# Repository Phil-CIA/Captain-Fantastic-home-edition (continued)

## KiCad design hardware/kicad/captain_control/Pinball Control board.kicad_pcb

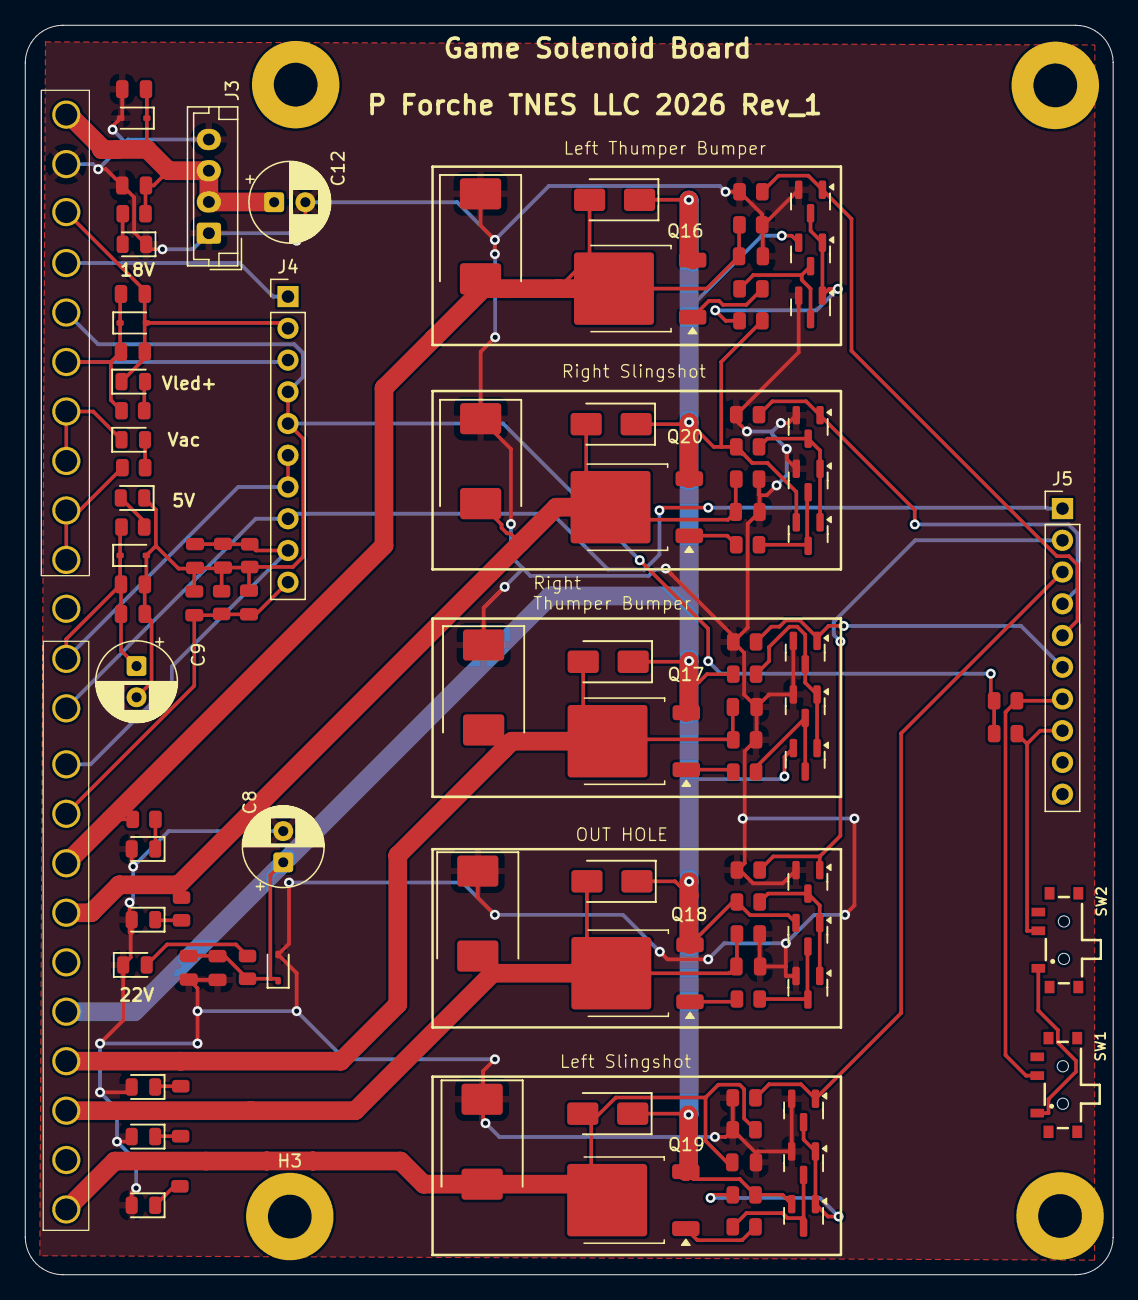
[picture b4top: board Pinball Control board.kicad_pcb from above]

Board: 2 copper layers, 87.1 x 100.0 mm, 108 parts (0 on the bottom side), 51 nets.

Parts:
C1, C2, C3, C6, C7, C13: 1uF; C_0805
C4, C5, C10, C11, C14, C15, C19, C20, C21, C22, C23: 100nF; C_0805
C8, C9, C12: 100uf, 35V; CP_Radial_D6.3mm_P2.50mm
D1, D21, D22, D23, D24, D25: Red; D_0805
D2: Yellow; D_0805
D3, D4, D7, D8: 1N5819WS; D_SOD-323
D5: Green; D_0805
D6, D19: White; D_0805
D9, D11, D13, D15, D17: US1M; D_SMA
D10, D12, D14, D16, D18: SMCJ30CA; D_SMC
H1, H2, H3, H4: MountingHole; MountingHole_3.5mm_Pad
J1: Connector C; CONN_SDA-41792_M450_23_MOL
J3: B4B-XH-A; JST_EH_B4B-EH-A_1x04_P2.50mm_Vertical
J4, J5: Conn_01x10_Pin; PinHeader_1x10_P2.54mm_Vertical
Q1, Q2, Q3, Q4, Q5, Q7, Q9, Q11, Q13, Q15: BSS138; Q_SOT-23
Q6, Q8, Q10, Q12, Q14: BSS84; Q_SOT-23
Q16, Q17, Q18, Q19, Q20: IRFR5410; TO-252-2
R1, R8, R34, R37, R50, R51, R52: 2.4kΩ; R_0805
R2, R4: 680Ω; R_0805
R3: 4.7Ω; R_0805
R5: 4.7kΩ; R_0805
R6, R7, R14, R15, R16, R17, R18, R19, R20, R21, R22, R23, R29, R30, R31, R32, R33: 10kΩ; R_0805
R24, R25, R26, R27, R28: 56Ω; R_0805
R38: 270Ω; R_0805
SW1, SW2: test switch; Slide Sw LCSC#C7498220

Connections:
3V3: J1.13, J4.8, J5.1
5.6vac: D19.1, J1.7, J1.8
5.6vac com: J1.9, J1.10, R38.1
+3V3: SW1.1 (A), SW2.1 (A)
+5V: C3.1, C5.1, C9.1, D4.1, J1.12, J4.6, J4.7, R2.2
+18vdc: C7.1, C11.1, C12.1, D7.1, J1.1, J3.2, J3.3, R5.2
+22vdc: C2.1, C4.1, C8.1, D3.1, D9.1, D11.1, D13.1, D15.1, D17.1, J1.19, Q6.2 (S), Q8.2 (S), Q10.2 (S), Q12.2 (S), Q14.2 (S), Q16.3 (S), Q17.3 (S), Q18.3 (S), Q19.3 (S), Q20.3 (S), R3.2, R19.2, R20.2, R21.2, R22.2, R23.2
GND: C1.2, C3.2, C5.2, C9.2, C13.2, C14.2, C15.2, D1.1, D4.2, J1.5, J4.4, J4.5, R1.1, R6.2, R7.2, R8.1
GND (matrix GND1): C2.2, C4.2, C7.2, C8.2, C11.2, C12.2, C19.2, C20.2, C21.2, C22.2, C23.2, D2.1, D3.2, D6.1, D7.2, D10.1, D12.1, D14.1, D16.1, D18.1, D21.2, D22.2, D23.2, D24.2, D25.2, J1.2, J3.1, J3.4, Q1.2 (S), Q2.2 (S), Q3.2 (S), Q4.2 (S), Q5.2 (S), Q7.2 (S), Q9.2 (S), Q11.2 (S), Q13.2 (S), Q15.2 (S), R14.1, R15.1, R16.1, R17.1, R18.1, R29.1, R30.1, R31.1, R32.1, R33.1
unnamed: D1.2, R2.1
unnamed: D2.2, R3.1
unnamed: D5.2, R4.1
unnamed: D6.2, R5.1
unnamed: D19.2, R38.2
unnamed: D21.1, R34.1
unnamed: D22.1, R37.1
unnamed: D23.1, R50.1
unnamed: D24.1, R51.1
unnamed: D25.1, R52.1
unnamed: Q1.3 (D), Q6.1 (G), Q7.1 (G), R19.1
unnamed: Q2.3 (D), Q8.1 (G), Q9.1 (G), R20.1
unnamed: Q6.3 (D), Q7.3 (D), R24.1
unnamed: Q8.3 (D), Q9.3 (D), R25.1
unnamed: Q10.3 (D), Q11.3 (D), R26.1
unnamed: Q3.3 (D), Q10.1 (G), Q11.1 (G), R21.1
unnamed: Q12.3 (D), Q13.3 (D), R27.1
unnamed: Q4.3 (D), Q12.1 (G), Q13.1 (G), R22.1
unnamed: Q14.3 (D), Q15.3 (D), R28.1
unnamed: Q5.3 (D), Q14.1 (G), Q15.1 (G), R23.1
unnamed: Q16.1 (G), R24.2
unnamed: Q17.1 (G), R25.2
unnamed: Q18.1 (G), R26.2
unnamed: Q19.1 (G), R27.2
unnamed: Q20.1 (G), R28.2
S2: J5.2, Q3.1 (G), R16.2
S3: J5.3, Q4.1 (G), R17.2
S4: J5.4, Q5.1 (G), R18.2
S5: J5.5, Q1.1 (G), R14.2
S6: J5.6, Q2.1 (G), R15.2
SD2: C21.1, D13.2, D14.2, J1.21, Q18.2 (D), R31.2, R52.2
SD3: C19.1, D15.2, D16.2, J1.23, Q19.2 (D), R32.2, R51.2
SD4: C22.1, D17.2, D18.2, J1.17, Q20.2 (D), R33.2, R50.2
SD5: C20.1, D9.2, D10.2, J1.16, Q16.2 (D), R29.2, R34.2
SD6: C23.1, D11.2, D12.2, J1.20, Q17.2 (D), R30.2, R37.2
SW1: J5.7, R6.1, SW1.2 (B)
SW2: J5.8, R7.1, SW2.2 (B)
Start: C13.1, C15.1, J1.15, J4.10, R8.2
Tilt: C1.1, C14.1, J1.14, J4.9, R1.2
To Speaker: J1.4, J4.1
Vled: C6.1, C10.1, D8.1, J1.6, J4.3, R4.2
Vled Ret: C6.2, C10.2, D5.1, D8.2, J1.3, J4.2

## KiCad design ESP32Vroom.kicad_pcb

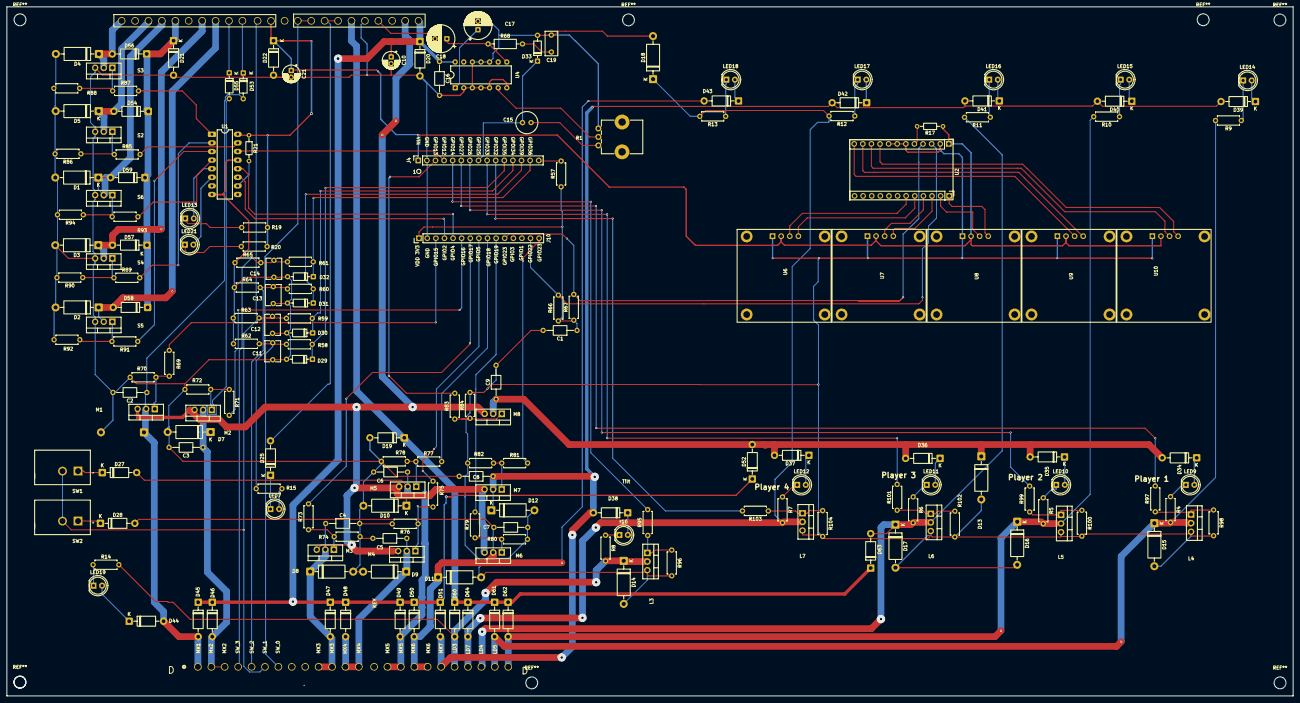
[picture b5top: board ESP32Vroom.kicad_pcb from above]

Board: 2 copper layers, 379.7 x 203.4 mm, 192 parts (1 on the bottom side), 128 nets.

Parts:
C1, C2, C3, C4, C5, C6, C7, C8, C9, C16: 0.1uf 50v; C_Axial_L3.8mm_D2.6mm_P10.00mm_Horizontal
C10, C21: 22uf 25v; CP_Radial_D5.0mm_P2.00mm
C11, C12, C13, C14: 100nf; C_Disc_D6.0mm_W4.4mm_P5.00mm
C15: 100uf 16v; C_Radial_D6.3mm_H11.0mm_P2.50mm
C17: 5uf; CP_Radial_D8.0mm_P2.50mm
C18: 500uf; CP_Radial_D8.0mm_P3.50mm
C19: 0.1uf; C_Rect_L7.0mm_W3.5mm_P5.00mm
D1, D2, D3, D4, D5: P6KE30A; D_DO-15_P12.70mm_Horizontal
D6, D7, D8, D9, D10, D11, D12, D13: P6KE20A; D_DO-15_P12.70mm_Horizontal
D14, D15, D16, D17, D18: P6KE6.8A; D_DO-15_P12.70mm_Horizontal
D19, D20, D21, D22: 1N5819; D_DO-41_SOD81_P10.16mm_Horizontal
D25, D27, D28, D34, D35, D36, D37, D38, D39, D40, D41, D42, D43, D44: 1N4001; D_DO-41_SOD81_P10.16mm_Horizontal
D29, D30, D31, D32, D33, D53, D55: 1N4148; D_DO-35_SOD27_P7.62mm_Horizontal
D45, D46, D47, D48, D49, D50, D51, D52, D54, D56, D57, D58, D59, D60, D61, D62, D63, D64: UF4007; D_DO-41_SOD81_P10.16mm_Horizontal
J4: Connector_esp32_1x15; PinSocket_1x15_P2.54mm_Vertical
J10: J 10
J12: Connector C; CONN_SDA-41792_M450_23_MOL
JD2: connector "d"; Connector D
L3, L4, L5, L6, L7: IRLZ44NPBF; TO-220-3_Vertical
LED7: Display lite; LED_D5.0mm_IRBlack
LED9: Player 1; LED_D5.0mm_IRBlack
LED10: Player 2; LED_D5.0mm_IRBlack
LED11: Player 3; LED_D5.0mm_IRBlack
LED12: Player 4; LED_D5.0mm_IRBlack
LED13: status; LED_D5.0mm_IRBlack
LED14: Ball 1; LED_D5.0mm_IRBlack
LED15: Ball 2; LED_D5.0mm_IRBlack
LED16: Ball 3; LED_D5.0mm_IRBlack
LED17: Ball 4; LED_D5.0mm_IRBlack
LED18: Ball 5; LED_D5.0mm_IRBlack
LED19: Game Over; LED_D5.0mm_IRBlack
LED21: Fail; LED_D5.0mm_IRBlack
M1, M2, M3, M4, M5, M6, M7, M8: IRLZ44NPBF; TO-220-3_Vertical
R1: 10k; Potentiometer_Bourns_PTV09A-1_Single_Vertical
R4, R5, R6, R7, R8, R9, R10, R11, R12, R13, R14: 680; R_Axial_DIN0207_L6.3mm_D2.5mm_P7.62mm_Horizontal
R15: 270; R_Axial_DIN0207_L6.3mm_D2.5mm_P7.62mm_Horizontal
R17, R21: 10k; R_Axial_DIN0204_L3.6mm_D1.6mm_P7.62mm_Horizontal
R19, R20: 470; R_Axial_DIN0207_L6.3mm_D2.5mm_P7.62mm_Horizontal
R57, R58, R59, R60, R61, R70, R72, R74, R76, R78, R80, R82, R84, R86, R88, R90, R92, R94, R96, R98, R100, R102, R104: 10k; R_Axial_DIN0207_L6.3mm_D2.5mm_P7.62mm_Horizontal
R62, R63, R64, R65: 2k; R_Axial_DIN0207_L6.3mm_D2.5mm_P7.62mm_Horizontal
R66, R67: 4.7k; R_Axial_DIN0207_L6.3mm_D2.5mm_P7.62mm_Horizontal
R68: 2.7; R_Axial_DIN0207_L6.3mm_D2.5mm_P10.16mm_Horizontal
R69, R71, R73, R75, R77, R79, R81, R83, R85, R87, R89, R91, R93, R95, R97, R99, R101, R103: 220; R_Axial_DIN0207_L6.3mm_D2.5mm_P7.62mm_Horizontal
S2, S3, S4, S5, S6: IRLZ44NPBF; TO-220-3_Vertical
SW1, SW2: test switch; SW_GF-123-0054
U1: 74HC595; DIP-16_W7.62mm_LongPads
U2: PCA9548ADB; Adafruit I2C mux
U4: LM384; DIP-14_W7.62mm
U6, U7, U8, U9, U10: 0.96 OLED display ssd1306; ).96 inOLED display SSD1306
r16: Tilt; LED_D5.0mm_IRBlack

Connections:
5.6vac: D25.2 (A), J12.7, J12.8
5.6vac com: J12.9, J12.10, R15.2
18vdc Ret: J12.2, M1.3 (S), M2.3 (S), M3.3 (S), M4.3 (S), M5.3 (S), M6.3 (S), M7.3 (S), M8.3 (S)
+3V3: C1.1, J10.16 (VDD_3V3), R57.1, R66.1, R67.1
+5V: C21.1, D22.1 (K), J4.1 (Vin), J12.12, R17.1, R19.1, R20.2, R21.1, U1.16 (VCC), U2.1 (Vcc), U6.2 (VCC), U7.2 (VCC), U8.2 (VCC), U9.2 (VCC), U10.2 (VCC)
+18vdc: C10.1, C16.1, D20.1 (K), D45.1 (K), D46.1 (K), D47.1 (K), D48.1 (K), D49.1 (K), D50.1 (K), D51.1 (K), D52.1 (K), J12.1, U4.14 (VS)
+22vdc: D21.1 (K), D54.1 (K), D56.1 (K), D57.1 (K), D58.1 (K), D59.1 (K), J12.19
Audio: C15.2, D33.1 (K), J4.8 (GPIO25)
GND: C1.2, C2.2, C3.2, C4.2, C5.2, C6.2, C7.2, C8.2, C9.2, C10.2, C11.2, C12.2, C13.2, C14.2, C16.2, C17.2, C19.2, C21.2, D1.2 (A), D2.2 (A), D3.2 (A), D4.2 (A), D5.2 (A), D6.2 (A), D7.2 (A), D8.2 (A), D9.2 (A), D10.2 (A), D11.2 (A), D12.2 (A), D13.2 (A), D14.2 (A), D15.2 (A), D16.2 (A), D17.2 (A), D18.2 (A), D19.2 (A), D20.2 (A), D21.2 (A), D22.2 (A), D29.2 (A), D30.2 (A), D31.2 (A), D32.2 (A), D33.2 (A), J4.2 (GND), J10.17 (GND), J12.5, L3.3 (S), L4.3 (S), L5.3 (S), L6.3 (S), L7.3 (S), R1.3, R62.1, R63.1, R64.1, R65.1, R70.2, R72.2, R74.2, R76.2, R78.2, R80.2, R82.2, R84.2, R86.2, R88.2, R90.2, R92.2, R94.2, R96.2, R98.2, R100.2, R102.2, R104.2, S2.3 (S), S3.3 (S), S4.3 (S), S5.3 (S), S6.3 (S), U1.8 (GND), U1.13 (~OE), U2.2 (Gnd), U2.6 (A0), U2.7 (A1), U2.8 (A2), U4.2 (+), U4.3 (GND), U4.4 (GND), U4.5 (GND), U4.7 (GND), U4.10 (GND), U4.11 (GND), U4.12 (GND), U6.1 (GND), U7.1 (GND), U8.1 (GND), U9.1 (GND), U10.1 (GND)
I2C SCL: J10.29 (I2C-SCL), R66.2, U2.3 (SDA_IN)
I2C SDA: J10.26 (I2C_SDA), R67.2, U2.4 (SCL_IN)
L3: J4.5 (GPIO14), R95.2
L4: J4.6 (GPIO27), R97.2
L5: J4.7 (GPIO26), R99.2
L6: J4.9 (GPIO33), R101.2
L7: J4.10 (GPIO32), R103.2
LD3: D14.1 (K), D60.2 (A), JD2.20, L3.2 (D), R8.2, R14.2
LD4: D15.1 (K), D61.2 (A), JD2.23, L4.2 (D), R4.2, R9.2
LD5: D16.1 (K), D62.2 (A), JD2.24, L5.2 (D), R5.2, R10.2
LD6: D17.1 (K), D63.2 (A), JD2.22, L6.2 (D), R6.2, R11.2
LD7: D18.1 (K), D64.2 (A), JD2.21, L7.2 (D), R7.2, R12.2, R13.2
M1: J10.18 (GPIO15), R69.2
M2: J10.21 (GPIO16), R71.2
M3: J10.22 (GPIO17), R73.2
M4: J10.23 (GPIO5), R75.2
M5: J10.24 (GPIO18), R77.2
M6: J10.25 (GPIO19), R79.2
M7: J10.30 (GPIO23), R81.2
M8: J4.3 (GPIO13), R83.2
MX1: C2.1, D6.1 (K), D44.2 (A), D45.2 (A), D53.2 (A), JD2.1, M1.2 (D)
MX2: C3.1, D7.1 (K), D46.2 (A), D55.2 (A), JD2.2, JD2.3, M2.2 (D)
MX3: C4.1, D8.1 (K), D47.2 (A), JD2.10, JD2.11, M3.2 (D)
MX4: C5.1, D9.1 (K), D48.2 (A), JD2.12, JD2.13, M4.2 (D)
MX5: C6.1, D10.1 (K), D27.2 (A), D49.2 (A), JD2.15, JD2.16, M5.2 (D)
MX6: C7.1, D11.1 (K), D28.2 (A), D43.2 (A), D50.2 (A), JD2.17, JD2.18, M6.2 (D)
MX7: C8.1, D12.1 (K), D38.2 (A), D39.2 (A), D40.2 (A), D41.2 (A), D42.2 (A), D51.2 (A), JD2.19, M7.2 (D)
MX8: C9.1, D13.1 (K), D34.2 (A), D35.2 (A), D36.2 (A), D37.2 (A), D52.2 (A), M8.2 (D)
unnamed: C15.1, R1.1
unnamed: C18.1, R68.1, U4.8
unnamed: C19.1, R68.2
unnamed: D25.1 (K), LED7.1 (K)
unnamed: D27.1 (K), SW1.1 (A)
unnamed: D28.1 (K), SW2.1 (A)
unnamed: D34.1 (K), LED9.2 (A)
unnamed: D35.1 (K), LED10.2 (A)
unnamed: D36.1 (K), LED11.2 (A)
unnamed: D37.1 (K), LED12.2 (A)
unnamed: D38.1 (K), r16.2 (A)
unnamed: D39.1 (K), LED14.2 (A)
unnamed: D40.1 (K), LED15.2 (A)
unnamed: D41.1 (K), LED16.2 (A)
unnamed: D42.1 (K), LED17.2 (A)
unnamed: D43.1 (K), LED18.2 (A)
unnamed: D44.1 (K), LED19.2 (A)
unnamed: D53.1 (K), J12.14
unnamed: D55.1 (K), J12.15
unnamed: J4.15 (EN_/_RESET), R57.2
unnamed: L3.1 (G), R95.1, R96.1
unnamed: L4.1 (G), R97.1, R98.1
unnamed: L5.1 (G), R99.1, R100.1
unnamed: L6.1 (G), R101.1, R102.1
unnamed: L7.1 (G), R103.1, R104.1
unnamed: LED7.2 (A), R15.1
unnamed: LED9.1 (K), R4.1
unnamed: LED10.1 (K), R5.1
unnamed: LED11.1 (K), R6.1
unnamed: LED12.1 (K), R7.1
unnamed: LED13.2 (A), U1.5 (QF)
unnamed: LED13.1 (K), R19.2
unnamed: LED14.1 (K), R9.1
unnamed: LED15.1 (K), R10.1
unnamed: LED16.1 (K), R11.1
unnamed: LED17.1 (K), R12.1
unnamed: LED18.1 (K), R13.1
unnamed: LED19.1 (K), R14.1
unnamed: LED21.2 (A), U1.6 (QG)
unnamed: LED21.1 (K), R20.1
unnamed: M1.1 (G), R69.1, R70.1
unnamed: M2.1 (G), R71.1, R72.1
unnamed: M3.1 (G), R73.1, R74.1
unnamed: M4.1 (G), R75.1, R76.1
unnamed: M5.1 (G), R77.1, R78.1
unnamed: M6.1 (G), R79.1, R80.1
unnamed: M7.1 (G), R81.1, R82.1
unnamed: M8.1 (G), R83.1, R84.1
unnamed: R85.1, R86.1, S2.1 (G)
unnamed: R87.1, R88.1, S3.1 (G)
unnamed: R89.1, R90.1, S4.1 (G)
unnamed: R91.1, R92.1, S5.1 (G)
unnamed: R93.1, R94.1, S6.1 (G)
unnamed: R21.2, U1.10 (~SRCLR)
unnamed: R17.2, U2.5 (Reset)
unnamed: R1.2, U4.6 (-)
unnamed: C17.1, U4.1 (BYPASS)
unnamed: R8.1, r16.1 (K)
S2: R85.2, U1.15 (QA)
S3: R87.2, U1.1 (QB)
S4: R89.2, U1.2 (QC)
S5: R91.2, U1.3 (QD)
S6: R93.2, U1.4 (QE)
SCL_0: U2.10 (SCL0), U10.3 (SLC)
SCL_1: U2.12 (SCL1), U9.3 (SLC)
SCL_2: U2.14 (SCL2), U8.3 (SLC)
SCL_3: U2.16 (SCL3), U7.3 (SLC)
SCL_4: U2.18 (SCL4), U6.3 (SLC)
SD2: D5.1 (K), D54.2 (A), J12.21, S2.2 (D)
SD3: D4.1 (K), D56.2 (A), J12.23, S3.2 (D)
SD4: D3.1 (K), D57.2 (A), J12.17, S4.2 (D)
SD5: D2.1 (K), D58.2 (A), J12.16, S5.2 (D)
SD6: D1.1 (K), D59.2 (A), J12.20, S6.2 (D)
SDA_0: U2.9 (SDA0), U10.4 (SDA)
SDA_1: U2.11 (SDA1), U9.4 (SDA)
SDA_2: U2.13 (SDA2), U8.4 (SDA)
SDA_3: U2.15 (SDA3), U7.4 (SDA)
SDA_4: U2.17 (SDA4), U6.4 (SDA)
SW1: D29.1 (K), J4.11 (GPIO35), R58.2
SW2: D30.1 (K), J4.12 (GPIO34), R59.2
SW3: D31.1 (K), J4.13 (GPIO39), R60.2
SW4: D32.1 (K), J4.14 (GPIO36), R61.2
SW_0: C11.1, JD2.7, R58.1, R62.2
SW_1: C12.1, J12.13, JD2.6, R59.1, R63.2, SW1.2 (B), SW2.2 (B)
SW_2: C13.1, JD2.5, R60.1, R64.2
SW_3: C14.1, JD2.4, R61.1, R65.2
To Speaker: C18.2, J12.4
Vled: D19.1 (K), D60.1 (K), D61.1 (K), D62.1 (K), D63.1 (K), D64.1 (K), J12.6
a0: J4.4 (GPIO12), U1.14 (SER)
a1: J10.20 (GPIO4), U1.12 (RCLK)
a2: J10.19 (GPIO2), U1.11 (SRCLK)

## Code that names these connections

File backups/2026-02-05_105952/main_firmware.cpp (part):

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// Row pins (M1-M8) - Shared between lamps and switches
// From schematic pin mapping table
const uint8_t rowPins[NUM_LAMP_ROWS] = {
    15, // M1 - GPIO15
    16, // M2 - GPIO16
    17, // M3 - GPIO17
    5,  // M4 - GPIO5
    18, // M5 - GPIO18
    19, // M6 - GPIO19
    23, // M7 - GPIO23
    13, // M8 - GPIO13
};

// Shift register pins (74HC595)
#define SR_DATA   2   // GPIO2 - Serial data
#define SR_CLOCK  12  // GPIO12 - Shift clock
#define SR_LATCH  4   // GPIO4 - Storage register clock

// Switch input pins
const uint8_t switchColPins[NUM_SWITCH_COLS] = {
    35, // SW1 - GPIO35
    34, // SW2 - GPIO34
    39, // SW3 - GPIO39
    36, // SW4 - GPIO36
};

// Shift register bit mapping (16 bits total)
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TaskHandle_t otaTaskHandle = NULL;  // Added task suspension for OTA updates

// ========== AUDIO SYSTEM DEFINITIONS ==========
// GPIO25 - DAC1 output to LM384N amplifier
#define AUDIO_PIN 25

// Sound effect IDs
enum SoundEffect {
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    SoundMessage msg;
    
    // Initialize DAC for sound effects
    dac_output_enable(DAC_CHANNEL_1);  // GPIO25
    dac_output_voltage(DAC_CHANNEL_1, 128);  // Center position (silence)
    
    Serial.println("[AUDIO] Audio system initialized on GPIO25");
    Serial.print("[AUDIO] Sound effects volume: ");
    Serial.println(audioVolume);
    Serial.println("[AUDIO] MP3 playback disabled - sound effects only");
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            delayMicroseconds(30);  // Wait for ringing to decay below threshold
            
            // 5. Read all switch columns for this row (while row still active)
            // GPIO34-39 have external pull-downs (or floating low)
            // Switch closed + row HIGH = column HIGH = true (CLOSED)
            // Switch open or row LOW = column LOW = false (OPEN)
            for (uint8_t col = 0; col < NUM_SWITCH_COLS; col++) {
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    Serial.println("Initializing shift register... [DONE]");
    
    // Initialize switch input pins
    // NOTE: GPIO34-39 are INPUT-ONLY and do NOT support internal pull-ups!
    // These pins likely have external pull-down resistors
    Serial.println("Initializing switch inputs (INPUT-ONLY pins, external pull-downs)...");
    for (uint8_t i = 0; i < NUM_SWITCH_COLS; i++) {
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
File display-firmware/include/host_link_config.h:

#ifndef HOST_LINK_CONFIG_H
#define HOST_LINK_CONFIG_H

// =============================================================================
// Host-Link SPI Slave + Handshake GPIO Configuration
// Target: ESP32-C6 DevKitM (Amazon clone, "C6 Mini")
// =============================================================================
//
// ESP32-C6 strapping-pin analysis (why GPIO0/GPIO1 are chosen):
//
//   GPIO8  – strapping pin: selects JTAG signal source at reset.
//             Driving it LOW externally routes JTAG to IO pins (can disrupt
//             USB-JTAG-based flashing).  → DO NOT use as handshake.
//
//   GPIO9  – strapping pin: boot-mode selector.  HIGH = SPI-Flash boot
//             (normal); LOW = Download/flash mode.  This is the BOOT button.
//             If the other board drives GPIO9 LOW during reset the chip will
//             enter download mode and refuse to boot normally.  → DO NOT use.
//
//   GPIO0  – NOT a strapping pin on ESP32-C6.  Safe to use as a handshake
//             line.  During reset the host board must hold this pin as an
//             input (high-Z), or a 10 kΩ pull-down keeps it at idle (LOW).
//
//   GPIO1  – NOT a strapping pin on ESP32-C6.  Safe as a handshake output
//             from the display side.  Drive LOW until firmware is ready.
//
// ─── Host-link SPI (display = SPI slave, host = SPI master) ─────────────────
//
//   GPIO4  MISO   – display → host data
//   GPIO5  CS     – active-LOW chip select, driven by host
//   GPIO6  MOSI   – host → display data
//   GPIO7  CLK    – SPI clock, driven by host
//
// ─── Handshake lines ─────────────────────────────────────────────────────────
//
//   GPIO0  HOST_REQ   – Host → Display, active-HIGH
//                       Host asserts HIGH to request a SPI transaction.
//                       Display polls/interrupts on this pin before clocking.
//                       Add 10 kΩ pull-down on display-board side so the pin
//                       reads LOW (idle) when the host board is unpowered or
//                       in reset.
//                       Add 470 Ω series resistor at the host-board output.
//
//   GPIO1  DISP_READY – Display → Host, active-HIGH
//                       Display drives HIGH when TX/RX buffers are prepared
//                       and a transaction can begin.  Host must only assert
//                       CS and start clocking after DISP_READY is HIGH.
//                       Display drives LOW on reset/init and immediately after
//                       a completed transaction until next buffer is queued.
//                       Add 470 Ω series resistor at the display-board output.
//
// ─── Electrical recommendations ──────────────────────────────────────────────
//
//   • 470 Ω series resistor on every inter-board signal (both SPI and handshake).
//   • 10 kΩ pull-down on HOST_REQ (GPIO0) at the display board so the pin
//     never floats when the host is unpowered.
//   • No strong pull-ups on GPIO0 or GPIO1 — idle state must be LOW.
//   • At power-on/reset both handshake pins must be high-Z or LOW; they must
//     NEVER be driven HIGH by external circuitry before firmware runs.
//   • Keep GPIO8 and GPIO9 free of external load at all times.
//
// =============================================================================

#include <Arduino.h>

// ─── SPI slave pins ───────────────────────────────────────────────────────────
constexpr uint8_t HOSTLINK_SPI_MISO_PIN = 4;
constexpr uint8_t HOSTLINK_SPI_CS_PIN   = 5;   // active-LOW, driven by host
constexpr uint8_t HOSTLINK_SPI_MOSI_PIN = 6;
constexpr uint8_t HOSTLINK_SPI_CLK_PIN  = 7;

// ─── Handshake pins ──────────────────────────────────────────────────────────
// HOST_REQ:   INPUT  on display board, OUTPUT on host board.
// DISP_READY: OUTPUT on display board, INPUT  on host board.
constexpr uint8_t HOSTLINK_HOST_REQ_PIN   = 0;   // Host → Display, active-HIGH
constexpr uint8_t HOSTLINK_DISP_READY_PIN = 1;   // Display → Host, active-HIGH

// ─── Polarity ─────────────────────────────────────────────────────────────────
// Both handshake lines are active-HIGH (1 = asserted, 0 = idle).
constexpr bool HOSTLINK_HANDSHAKE_ACTIVE_HIGH = true;

// ─── SPI transaction parameters ───────────────────────────────────────────────
constexpr uint32_t HOSTLINK_SPI_MAX_FREQ_HZ  = 10000000UL;  // 10 MHz max
constexpr uint8_t  HOSTLINK_SPI_MODE         = SPI_MODE0;
constexpr uint8_t  HOSTLINK_SPI_BIT_ORDER    = MSBFIRST;

// ─── Handshake timing ────────────────────────────────────────────────────────
// Maximum time the display will wait after asserting DISP_READY before it
// de-asserts (timeout guard, ms).
constexpr uint32_t HOSTLINK_READY_TIMEOUT_MS  = 100;
// Minimum LOW time (idle) on DISP_READY after a completed transaction before
// the next can be advertised (de-glitch gap, ms).
constexpr uint32_t HOSTLINK_READY_DEGLITCH_MS = 1;

#endif // HOST_LINK_CONFIG_H

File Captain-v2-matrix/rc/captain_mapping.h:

#ifndef CAPTAIN_MAPPING_H
#define CAPTAIN_MAPPING_H

#include <stddef.h>
#include <stdint.h>
#include "captain_protocol.h"

// Rows are generated by the shift-register chain; MCU switch column inputs are direct.
constexpr uint8_t CAPTAIN_MATRIX_ROW_PINS[CAPTAIN_SWITCH_ROWS] = {0, 1, 2, 3, 4, 5, 6, 7};
// Empirical switch bring-up mapping (2026-05-06):
// logical cols 0..3 map to MCU inputs GPIO20, GPIO18, GPIO21, GPIO19.
// This corrects the observed permutation where physical switch columns landed on
// the wrong logical columns during live matrix tests.
constexpr uint8_t CAPTAIN_MATRIX_SWITCH_COL_PINS[CAPTAIN_SWITCH_COLS] = {20, 18, 21, 19};

constexpr const char* CAPTAIN_SWITCH_NAMES[CAPTAIN_SWITCH_ROWS][CAPTAIN_SWITCH_COLS] = {
    {"S20 Outhole", "Tilt (moved to direct input)", "S11 Spinner R", "S22 Return Lane R"},
    {"S1 Lane A", "Start (moved to direct input)", "S6 Target 1", "S14 Slingshot L"},
    {"S2 Lane B", "S7 Bumper L", "S12 Side Switch", "S21 Return Lane L"},
    {"S3 Lane C", "S8 Bumper R", "S10 Spinner L", "S18 Bonus Lane L"},
    {"S4 Lane D", "Easy", "S9 Target 2", "S16 Slingshot R"},
    {"S5 Target 3", "Test", "S13 Side Switch", "S19 Bonus Lane R"},
    {"MX7 SW1", "MX7 SW2", "MX7 SW3", "MX7 SW4"},
    {"MX8 SW1", "MX8 SW2", "MX8 SW3", "MX8 SW4"}
};

constexpr const char* CAPTAIN_LAMP_NAMES[CAPTAIN_LAMP_ROWS][CAPTAIN_LAMP_COLS] = {
    {"Game Over", "Unused", "L12 8K Bonus", "L11 9K Bonus", "L22 Return Lane R"},
    {"Unused", "L1 A", "L14 6K Bonus", "L6 Target 1", "L19 1K Bonus"},
    {"Unused", "L2 B", "L15 5K Bonus", "L7 Double Bonus", "L21 Return Lane L"},
    {"Unused", "L3 C", "L13 7K Bonus", "L10 10K Bonus", "L18 2K Bonus"},
    {"Unused", "L4 D", "L17 3K Bonus", "L9 Target 2", "L20 Same Player"},
    {"Unused", "L5 Target 3", "L16 4K Bonus", "L8 Triple Bonus", "B5 Ball 5"},
    {"Unused", "B1 Ball 1", "B2 Ball 2", "B3 Ball 3", "B4 Ball 4"},
    {"Unused", "P1 Player 1", "P2 Player 2", "P3 Player 3", "P4 Player 4"}
};

inline size_t captainSwitchBitIndex(uint8_t row, uint8_t col) {
    return static_cast<size_t>(row) * CAPTAIN_SWITCH_COLS + col;
}

inline size_t captainLampBitIndex(uint8_t row, uint8_t col) {
    return static_cast<size_t>(row) * CAPTAIN_LAMP_COLS + col;
}

inline bool captainGetBit(const uint8_t* buffer, size_t bitIndex) {
    const size_t byteIndex = bitIndex / 8;
    const uint8_t mask = static_cast<uint8_t>(1u << (bitIndex % 8));
    return (buffer[byteIndex] & mask) != 0;
}

inline void captainSetBit(uint8_t* buffer, size_t bitIndex, bool state) {
    const size_t byteIndex = bitIndex / 8;
    const uint8_t mask = static_cast<uint8_t>(1u << (bitIndex % 8));
    if (state) {
        buffer[byteIndex] |= mask;
    } else {
        buffer[byteIndex] &= static_cast<uint8_t>(~mask);
    }
}

inline const char* captainSwitchName(uint8_t row, uint8_t col) {
    if (row >= CAPTAIN_SWITCH_ROWS || col >= CAPTAIN_SWITCH_COLS) {
        return "Unknown Switch";
    }
    return CAPTAIN_SWITCH_NAMES[row][col];
}

inline const char* captainLampName(uint8_t row, uint8_t col) {
    if (row >= CAPTAIN_LAMP_ROWS || col >= CAPTAIN_LAMP_COLS) {
        return "Unknown Lamp";
    }
    return CAPTAIN_LAMP_NAMES[row][col];
}

#endif

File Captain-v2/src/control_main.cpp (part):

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    }

    i2sAudioReady = true;
    Serial.printf("I2S audio ready (DIN=%u BCLK=%u LRCK=%u)\n", CAPTAIN_AUDIO_DIN_PIN, audioBclkPinEffective, audioLrckPinEffective);
    if (CAPTAIN_AUDIO_SWAP_BCLK_LRCK_FOR_TEST) {
        Serial.println("I2S pin test mode: BCLK/LRCK swapped in firmware");
    }
}

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
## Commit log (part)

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2026-02-05 Initial commit: Working RTOS firmware with External Flash OTA
    - All 5 RTOS tasks enabled (Audio, Matrix, Display, I/O, Game Logic)
    - External Flash OTA functional (W25Q64 8MB SPI flash)
    - Pre-erase optimization implemented (fixes sector race condition)
    - 100uF capacitor required at W25Q64 VCC (hardware fix documented)
    - Switch Mapping Mode disabled by default (enable with M command)
    - Clean production logging (92% reduction from debug version)
2026-03-26 Add Captain-v2 split-MPU project and clean workspace tasks
2026-03-26 Add project boundary map for repository cleanup
2026-03-26 Document WorkStation migration and local-only artifacts
2026-03-26 Normalize archive folder placement under archive/
2026-03-26 Normalize hardware files into kicad, gerbers, and backups structure
2026-03-26 Add repo index and end-of-day handoff docs
2026-03-28 Initial plan
2026-03-28 Finish PlatformIO/VS Code project and file organization
    Agent-Logs-Url: https://github.com/Phil-CIA/Captain-Fantastic-home-edition/sessions/f7ab7e0c-3dfb-4c8e-870a-6514de6f066c
2026-03-28 Add SPI handshake GPIO lines (GPIO0/IDC5=REQUEST, GPIO1/IDC9=READY) for display ESP32-C6
    Agent-Logs-Url: https://github.com/Phil-CIA/Captain-Fantastic-home-edition/sessions/c73ee4a7-705f-42b4-a4d8-dc867cf9c033
2026-03-28 feat: add ESP32-C6 display board firmware with GPIO4-7 SPI and GPIO0/1 handshake
    Agent-Logs-Url: https://github.com/Phil-CIA/Captain-Fantastic-home-edition/sessions/c1759bff-a03b-4d2e-ad8c-ad21d70d074b
2026-03-28 [display] Add ESP32-C6 display board pin config headers and flashing notes
    Agent-Logs-Url: https://github.com/Phil-CIA/Captain-Fantastic-home-edition/sessions/4c2f2f28-e107-4ede-88d8-686fd4951e46
2026-03-28 Add display-firmware scaffold and ESP32-C6 DevKitM Amazon clone pin documentation
    Agent-Logs-Url: https://github.com/Phil-CIA/Captain-Fantastic-home-edition/sessions/34400dec-5fcf-4ffa-8bd6-8ca02d875078
2026-03-28 feat(display-firmware): add GPIO0/GPIO1 handshake config and display-firmware scaffold for ESP32-C6
    Agent-Logs-Url: https://github.com/Phil-CIA/Captain-Fantastic-home-edition/sessions/0cddfb96-9512-4917-9402-31c3dfc88227
2026-03-31 Add files via upload
    Initial commit
2026-03-31 Add files via upload
    matrix board files
2026-03-31 Add files via upload
    display board commit
2026-03-31 Add files via upload
    conrtol board
2026-03-31 refactor(hardware): Organize v2 boards into clean kicad/ structure
    - Move Pinball Control board → hardware/kicad/captain_control/ (main ESP32)
    - Move Pinball matrix board → hardware/kicad/captain_matrix/ (matrix ESP32)
    - Move 7 Seg project → hardware/kicad/7seg_display/ (I2C HT16K33 display)
    - Archive Hat board → hardware/kicad/legacy/ (old single-board design)
    Update documentation to reflect v2 hardware layout:
    - hardware/README.txt: describe new board locations and roles
2026-03-31 feat(matrix): add HT16K33-style matrix interface, test harness, and board-specific projects
2026-03-31 docs(handoff): refresh repo state for matrix-first workflow
2026-03-31 refactor(screenshots): organize schematic photographs into hardware folder
2026-03-31 refactor(hardware): organize .net schematic netlists into board-specific folders
2026-03-31 refactor(hardware): move control-hat snapshots into captain_control screenshots folder
2026-03-31 feat(alignment): sync control audio and matrix C6 pin mapping with schematics
2026-03-31 feat(matrix-idf): scaffold ESP32-C6 ESP-IDF baseline without explicit FreeRTOS loop APIs
2026-03-31 feat(matrix-idf): port register I2C, switch scan, and lamp refresh into C6 ESP-IDF app
2026-03-31 docs(matrix): add redesign parking lot and March 31 handoff
2026-04-01 docs: 2026-04-01 session handoff and GPIO2/GPIO4 pin-sharing observation
    Agent-Logs-Url: https://github.com/Phil-CIA/Captain-Fantastic-home-edition/sessions/0a5cfc1f-a07f-43a4-9173-95130388fbca
2026-04-01 Add ESP32-C6 USB driver guide, matrix FLASHING_NOTES, platformio.ini COM port settings
    Agent-Logs-Url: https://github.com/Phil-CIA/Captain-Fantastic-home-edition/sessions/6df9d73a-40bc-4961-9b1d-11e98ef5d681
2026-04-01 Captain-v2 C6 bring-up: UART workflow, strap fix docs, matrix remap scaffold
2026-04-16 Add system behavior contract and index pointer
2026-04-18 Captain-v2: add matrix link supervision and 4MB matrix flash config
2026-04-30 matrix bring-up: align pin map to current schematic, add SR mapping controls, and add 2026-04-30 handoff
2026-05-01 Add bare-bones matrix test track and 2026-05-01 handoff
2026-05-01 Align matrix flash-size config to 2MB
2026-05-02 barebones: add column-595 isolation test mode, arm outputs, set chain col-then-row
    - Add BarebonesTestMode enum: Column595Isolation and SingleLampPulse
    - Default mode set to Column595Isolation
    - TEST_ENABLE_OUTPUTS = true (armed for bench test)
    - TEST_FORCE_OE_LOW_WHEN_ENABLED = true (OE held steady low, no blanking)
    - SR_CHAIN_IS_COL_THEN_ROW = true (aligns with U4->U5 schematic chain)
    - Pattern: 0xAA, 0x55, walking 1s 0x01..0x80, 700ms hold per step
2026-05-03 matrix barebones: lock baseline_2026_05_03_low_stress profile
    - Pin profile name tag and log it at boot for firmware identification
    - Reduce TEST_ON_US from 350ms to 180ms to protect bulbs during bring-up
    - Walk timing unchanged: 1s period, phased row-settle sequence
    - Polarity/chain settings verified working on hardware (first lamp lit)
    - SR_CHAIN_IS_COL_THEN_ROW=true, ROW/COL active-high confirmed good
    - Paused here: stable known-good baseline flashed to COM4
2026-05-04 matrix barebones: Phase 1 - ControlDrivenScan canonical runtime sequence
    New mode: BarebonesTestMode::ControlDrivenScan (active)
    Implements the canonical production row-scan sequence entirely in barebones
    outside app_main - same pattern as refreshLampMatrixStep() in production but
    validated independently on proven bring-up polarity/chain settings before any
    changes to the production runtime.
    State sequence per row (A->B->C->D):
2026-05-04 matrix barebones: Phase 2 matrix-pattern fast scan validated
    - Keep ControlDrivenScan as active test mode
    - Fast multiplex timings for persistence-of-vision (100us blank, 100us settle, 700us on, 100us post-hold)
    - Replace headbox chase feed with matrix control pattern source (mirrors writeMatrixCommand)
    - Pattern now drives row-byte lamp data matching matrix domain (not headbox LEDs)
    - Serial command path remains disabled by default; script source drives lampRam for deterministic bench tests
    - Hardware validation confirmed: expected row scan and visible lamp behavior
2026-05-04 Checkpoint handoff: matrix timing debug state and link diagnostics
2026-05-05 matrix: apply logical-to-physical col remap (drop col0, shift cols 1-4 to 0-3)
    Hardware-verified on bench: physical lamp column harness is offset by +1
    from software addressing. Fix: remapLogicalToPhysicalCols() shifts the
    logical col mask right by 1 bit at SR frame compose time.
    - matrix_app_main.cpp: remap applied inside composeShiftFrame() so all
    scan paths (normal, diag, boot test, safe proof) are covered
    - matrix_barebones_main.cpp: remap applied in runTargetLampSequenceLoop();
2026-05-05 matrix: fix LED flicker and reduce brightness for 18V operation
    Phase 8 - multiplex LED brightness tuning (2026-05-05)
    - CDS_COLUMN_ON_US: 700us -> 350us (~35% duty cycle per row slot)
    LEDs are automotive 12V-rated running at 18V; halved on-time keeps
    brightness acceptable without over-driving them further
    - vTaskDelay yield: every 10 cycles (~80ms gap) -> every 250 cycles (~1.3s)
    10ms dark gap every 80ms was visible flicker with LEDs (no thermal lag
2026-05-05 matrix: fix production scan vTaskDelay flicker; restore default_envs
    - matrix_app_main.cpp: replace bare vTaskDelay(1) every loop with
    counter-gated yield every 250 refreshLampMatrixStep() calls (~1.3s
    between 10ms gaps). Same fix as barebones firmware. Eliminates LED
    flicker visible at 12Hz with no thermal lag (unlike tungsten).
    - platformio.ini: default_envs restored to captain_matrix_idf
    Production firmware uploaded to COM4 at this commit.
2026-05-05 control: replace fixed matrix lamp write with explicit blink bring-up quartet
    - Remove hardcoded always-on test set that forced matrix lamps each poll
    (L22, L2, L13), which could be mistaken for stale lamp data.
    - Add deterministic link bring-up blink pattern at 500ms:
    L2, L7, L10, L20 (same quartet validated on matrix board tests).
    - writeMatrixCommand now takes current time and toggles lamp rows on/off
    each half-second for clear I2C link visibility.
2026-05-05 control: disable test blink for steady matrix lamps; tune COM5 upload settings
    - control_main.cpp: add MATRIX_TEST_BLINK_ENABLED=false so the matrix
    bring-up quartet (L2/L7/L10/L20) is steady instead of 500ms blink
    - platformio.ini (captain_control): keep upload_speed=57600 and use
    --no-stub upload flag to improve behavior on unstable CP210x COM5 link
2026-05-05 control: lower COM5 upload speed to 38400 for stable flashing
2026-05-05 matrix: make watchdog yield time-based to reduce periodic LED flicker
    - matrix_app_main.cpp: replace scan-cycle-based vTaskDelay(1) trigger with
    wall-clock cadence (every 2s)
    - prevents workload-dependent 10ms dark gaps (more frequent when fewer rows
    are lit), which can appear as periodic flicker with LEDs
    Production firmware uploaded to COM4 at this commit.
2026-05-05 matrix: deterministic scan timing - fixed-slot wall-clock delays
    Key changes:
    - Add delayWallUs() helper using esp_timer_get_time() hardware counter;
    immune to I2C interrupt jitter that made esp_rom_delay_us exit early
    - All scan phases (blank, settle, pulse, post-hold) now use wall-clock delays
    - Pulse/post-hold window runs every row regardless of colMask so row slot
    duration is constant and does not vary with lamp pattern density
2026-05-05 matrix: chunked OLED milestone + EOD handoff 2026-05-05
2026-05-07 cleanup: remove all bringup/diag dead code from matrix and control firmware
    matrix_app_main.cpp:
    - Remove entire OLED subsystem (~350 lines): all oled* functions, constants,
    variables (OLED_REFRESH_MS, OLED_I2C_SDA/SCL_PIN, CAPTAIN_MATRIX_ENABLE_OLED_DIAGNOSTICS, etc.)
    - Remove all diagnostic mode constants and runtime state: MATRIX_SAFE_PROOF_MODE,
    MATRIX_DIAG_GUARDED_BOOT_TEST, MATRIX_DIAG_FORCE_SINGLE_LAMP,
    MATRIX_DIAG_FREEZE_LAMP_DATA, MATRIX_DIAG_HOLD_ONE_LAMP_DC, etc.
2026-05-10 Add end-of-day handoff for 2026-05-10
2026-05-12 matrix: implement WS2812 heartbeat on GPIO8 via native RMT; control: move heartbeat to GPIO16 (GPIO2 conflict resolution); add handoff documentation
2026-05-13 2026-05-13: Remove unused scanSwitchMatrix() function (wrapped with #if 0); verified I2C stability over 5-min extended test; all systems nominal
2026-05-13 2026-05-13: Add end-of-day handoff - confirmed LED heartbeat, cleaned unused function, validated I2C stability (5-min test, 0.005% error rate)
2026-05-13 2026-05-13: Control heartbeat LED on GPIO15 as WS2812 (NeoPixel); replace plain GPIO toggle
2026-05-13 docs: update end-of-day handoff for 2026-05-13
2026-05-14 docs: append gameplay integration next steps to 2026-05-13 handoff
2026-05-14 Document matrix ghost-input investigation
2026-05-15 bringup: checkpoint gameplay and flicker triage
2026-05-25 Checkpoint from VS Code for cloud agent session
2026-06-05 Control: add bright graphic-zone gameplay LEDs with validated monitor workflow
2026-06-05 Closeout: capture remaining matrix and handoff updates
2026-06-05 docs: add switch latency phase-1 scope to handoff
2026-06-09 docs: add audio sound model and 2026-06-09 handoff
